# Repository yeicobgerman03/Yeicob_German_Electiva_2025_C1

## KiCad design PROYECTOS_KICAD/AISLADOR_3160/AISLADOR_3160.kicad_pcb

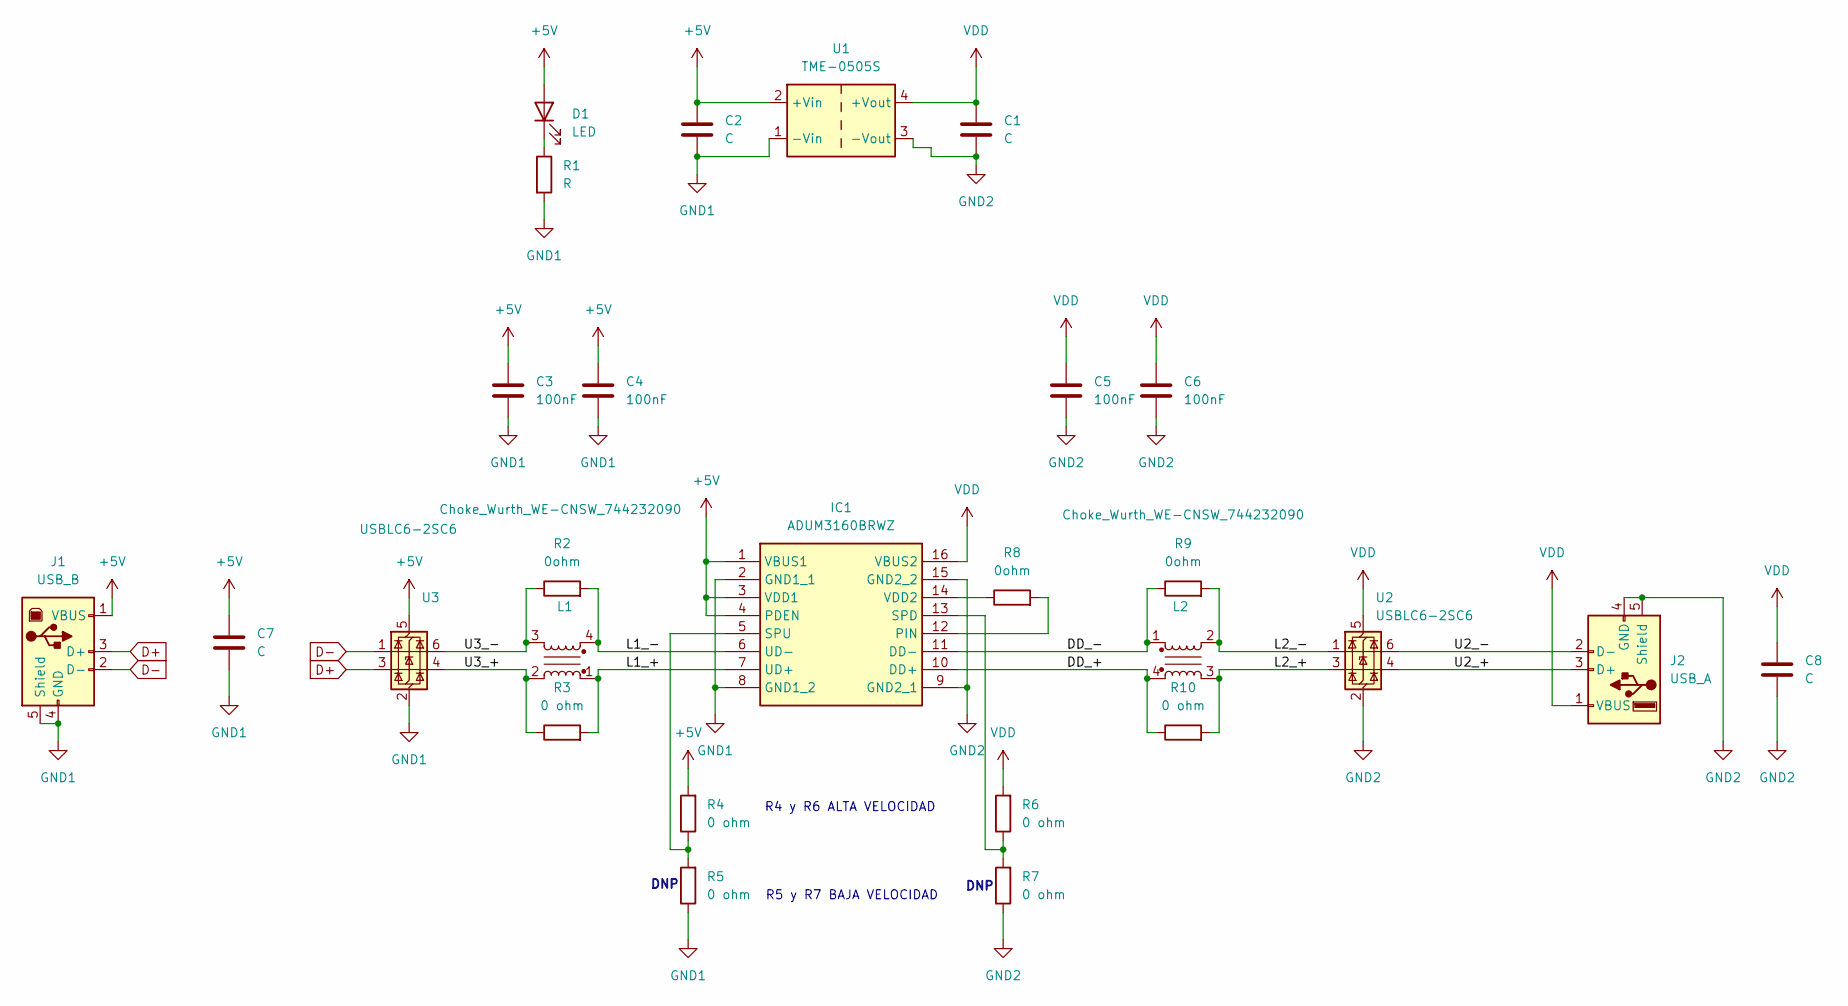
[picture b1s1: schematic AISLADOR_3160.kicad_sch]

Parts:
C1, C2: C; C_0603_1608Metric
C3, C4, C5, C6: 100nF; C_0603_1608Metric
C7, C8: C; CP_Elec_5x5.4
D1: LED; LED_0402_1005Metric
IC1: ADUM3160BRWZ; SOIC127P1032X265-16N; Manufacturer_Part_Number ADUM3160BRWZ; Mouser Part Number 584-ADUM3160BRWZ
J1: USB_B; USB_B_Lumberg_2411_02_Horizontal
J2: USB_A; USB_A_Molex_67643_Horizontal
L1, L2: Choke_Wurth_WE-CNSW_744232090; L_CommonMode_Wurth_WE-CNSW-1206
R1: R; R_0402_1005Metric
R2, R8, R9: 0ohm; R_0603_1608Metric
R3, R4, R5, R6, R7, R10: 0 ohm; R_0603_1608Metric
U1: TME-0505S; Converter_DCDC_TRACO_TME_03xxS_05xxS_12xxS_Single_THT
U2, U3: USBLC6-2SC6; SOT-23-6

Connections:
+5V: C2.1, C3.1, C4.1, C7.1, D1.2 (A), IC1.1 (VBUS1), IC1.3 (VDD1), IC1.4 (PDEN), J1.1 (VBUS), R4.2, U1.2 (+Vin), U3.5 (VBUS)
D+: J1.3 (D+), U3.3 (I/O2)
D-: J1.2 (D-), U3.1 (I/O1)
DD_+: IC1.10 (DD+), L2.4, R10.1
DD_-: IC1.11 (DD-), L2.1, R9.1
GND1: C2.2, C3.2, C4.2, C7.2, IC1.2 (GND1_1), IC1.8 (GND1_2), J1.4 (GND), J1.5 (Shield), R1.2, R5.1, U1.1 (-Vin), U3.2 (GND)
GND2: C1.2, C5.2, C6.2, C8.2, IC1.9 (GND2_1), IC1.15 (GND2_2), J2.4 (GND), J2.5 (Shield), R7.1, U1.3 (-Vout), U2.2 (GND)
L1_+: IC1.7 (UD+), L1.1, R3.2
L1_-: IC1.6 (UD-), L1.4, R2.2
L2_+: L2.3, R10.2, U2.3 (I/O2)
L2_-: L2.2, R9.2, U2.1 (I/O1)
unnamed: D1.1 (K), R1.1
unnamed: IC1.12 (PIN), R8.2
unnamed: IC1.13 (SPD), R6.1, R7.2
unnamed: IC1.5 (SPU), R4.1, R5.2
unnamed: IC1.14 (VDD2), R8.1
U2_+: J2.3 (D+), U2.4 (I/O2)
U2_-: J2.2 (D-), U2.6 (I/O1)
U3_+: L1.2, R3.1, U3.4 (I/O2)
U3_-: L1.3, R2.1, U3.6 (I/O1)
VDD: C1.1, C5.1, C6.1, C8.1, IC1.16 (VBUS2), J2.1 (VBUS), R6.2, U1.4 (+Vout), U2.5 (VBUS)

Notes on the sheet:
R5 y R7 BAJA VELOCIDAD
R4 y R6 ALTA VELOCIDAD
DNP

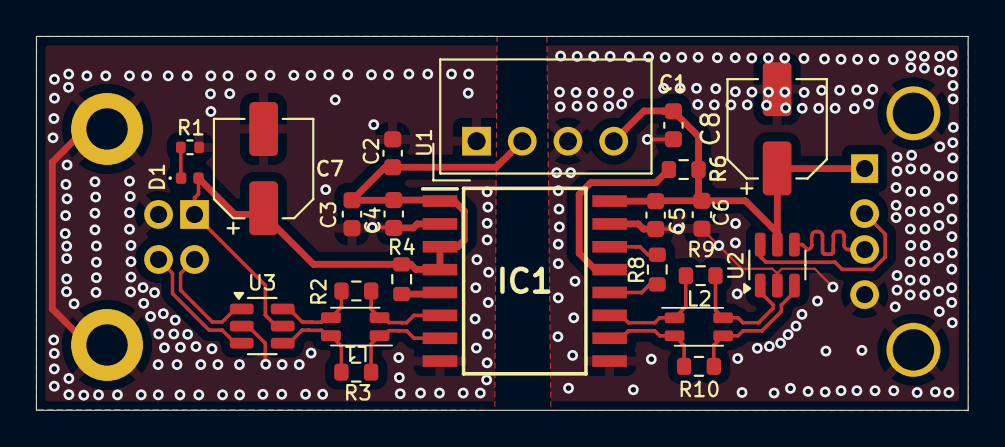
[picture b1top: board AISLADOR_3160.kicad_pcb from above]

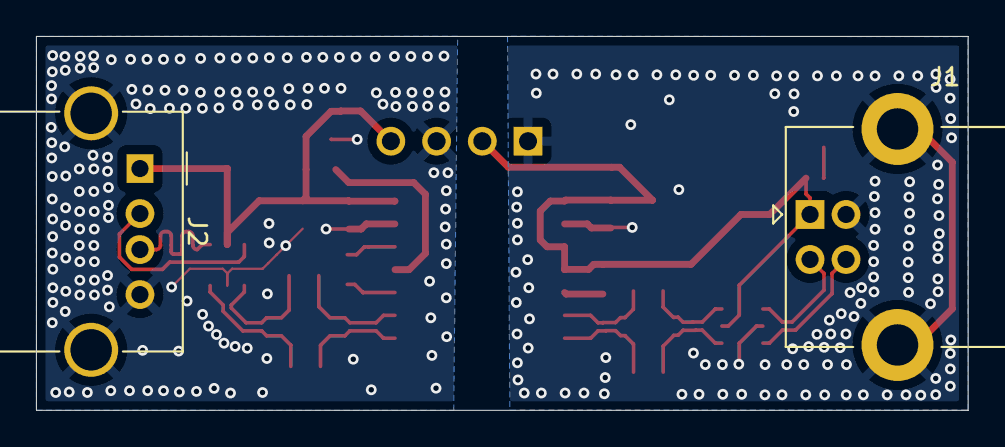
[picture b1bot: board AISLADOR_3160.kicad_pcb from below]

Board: 2 copper layers, 51.8 x 20.8 mm, 25 parts (2 on the bottom side), 21 nets.

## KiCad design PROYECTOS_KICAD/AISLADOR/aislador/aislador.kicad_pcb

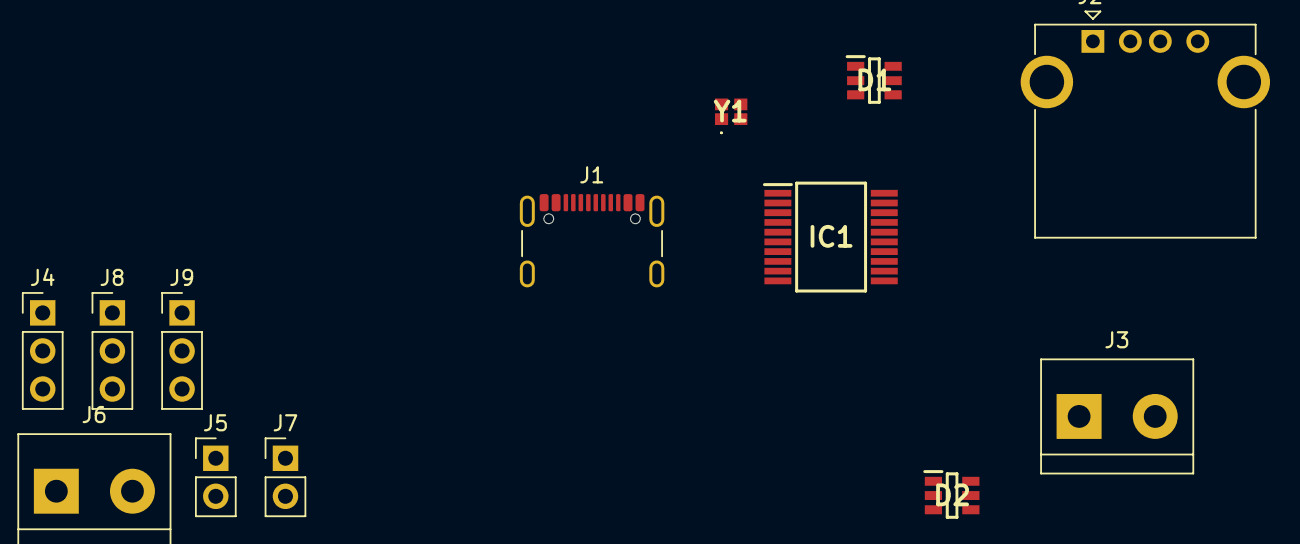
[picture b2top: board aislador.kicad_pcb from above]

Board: 2 copper layers, 13 parts (0 on the bottom side), 6 nets, no tracks yet.

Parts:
D1, D2: 82402304; SOT95P280X145-6N
IC1: ADUM3165BRSZ-RL; SOP65P780X200-20N
J1: USB_C_Receptacle_USB2.0_16P; USB_C_Receptacle_GCT_USB4105-xx-A_16P_TopMnt_Horizontal
J2: USB_A; USB_A_CONNFLY_DS1095-WNR0
J3, J6: Screw_Terminal_01x02; TerminalBlock_bornier-2_P5.08mm
J4, J8, J9: Conn_01x03_Pin; PinHeader_1x03_P2.54mm_Vertical
J5, J7: Conn_01x02_Pin; PinHeader_1x02_P2.54mm_Vertical
Y1: LFXTAL071257Reel

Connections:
GND1: J3.1, J8.2, J8.3, J9.2, J9.3
unnamed: IC1.1 (VBUS1), J4.2, J5.1, J7.1, J8.1
unnamed: IC1.3 (VDD1), J4.1, J9.1
unnamed: J1.A1 (GND), J1.A12 (GND), J1.B1 (GND), J1.B12 (GND)
unnamed: J1.A4 (VBUS), J1.A9 (VBUS), J1.B4 (VBUS), J1.B9 (VBUS)
unnamed: J3.2, J5.2

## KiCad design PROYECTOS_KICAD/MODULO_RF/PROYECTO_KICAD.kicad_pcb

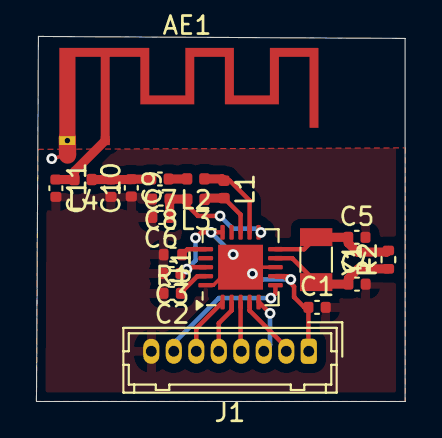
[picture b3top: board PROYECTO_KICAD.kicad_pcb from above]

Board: 2 copper layers, 20.5 x 20.3 mm, 21 parts (0 on the bottom side), 17 nets.

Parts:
AE1: Antenna; Texas_SWRA117D_2.4GHz_Right
C1: 10n; C_0402_1005Metric
C2: 33n; C_0402_1005Metric
C3: 1n; C_0402_1005Metric
C4, C5: 22p; C_0402_1005Metric
C6, C8: C_Small; C_0402_1005Metric
C7: 1p5; C_0402_1005Metric
C9: 1p; C_0402_1005Metric
C10, C11: Cx; C_0402_1005Metric
J1: Conn_01x08_Pin; Hirose_DF13-08P-1.25DSA_1x08_P1.25mm_Vertical
L1: 8n2; L_0402_1005Metric
L2: 3n9; L_0402_1005Metric
L3: 2n7; L_0402_1005Metric
L4: Lx; L_0402_1005Metric
R1: 22k; R_0402_1005Metric
R2: 16MHz; R_0402_1005Metric
U1: NRF24L01; QFN-20-1EP_4x4mm_P0.5mm_EP2.5x2.5mm
Y1: Crystal; Crystal_SMD_3215-2Pin_3.2x1.5mm

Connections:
GND: C1.1, C1.2, C2.2, C3.1, C3.2, C4.2, C5.2, C6.2, C8.2, C9.2, C10.2, C11.2, J1.1, J1.8, R1.2, U1.7 (VDD), U1.8 (VSS), U1.14 (VSS), U1.15 (VDD), U1.17 (VSS), U1.18 (VDD), U1.20 (VSS), U1.21
unnamed: AE1.1 (A), C11.1, L4.2
unnamed: C7.1, L2.2
unnamed: C7.2, C9.1, C10.1, L4.1
unnamed: J1.2, U1.4 (MOSI)
unnamed: J1.3, U1.5 (MISO)
unnamed: J1.4, U1.3 (SCK)
unnamed: J1.5, U1.2 (CSN)
unnamed: J1.6, U1.1 (CE)
unnamed: J1.7, U1.6 (IRQ)
unnamed: L1.1, L2.1, U1.12 (ANT1)
unnamed: L1.2, L3.1, U1.13 (ANT2)
unnamed: C2.1, U1.19 (DVDD)
unnamed: R1.1, U1.16 (IREF)
unnamed: C6.1, C8.1, L3.2, U1.11 (VDD_PA)
unnamed: C5.1, R2.2, U1.10 (XC1), Y1.2
unnamed: C4.1, R2.1, U1.9 (XC2), Y1.1

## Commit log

2025-01-20 proyecto en Kicad
2025-02-11 tarea
2025-03-07 avance
2025-03-12 aislador_3160
2025-03-12 aislador
2025-04-24 Diseño en solid edge
2025-04-25 proyecto
